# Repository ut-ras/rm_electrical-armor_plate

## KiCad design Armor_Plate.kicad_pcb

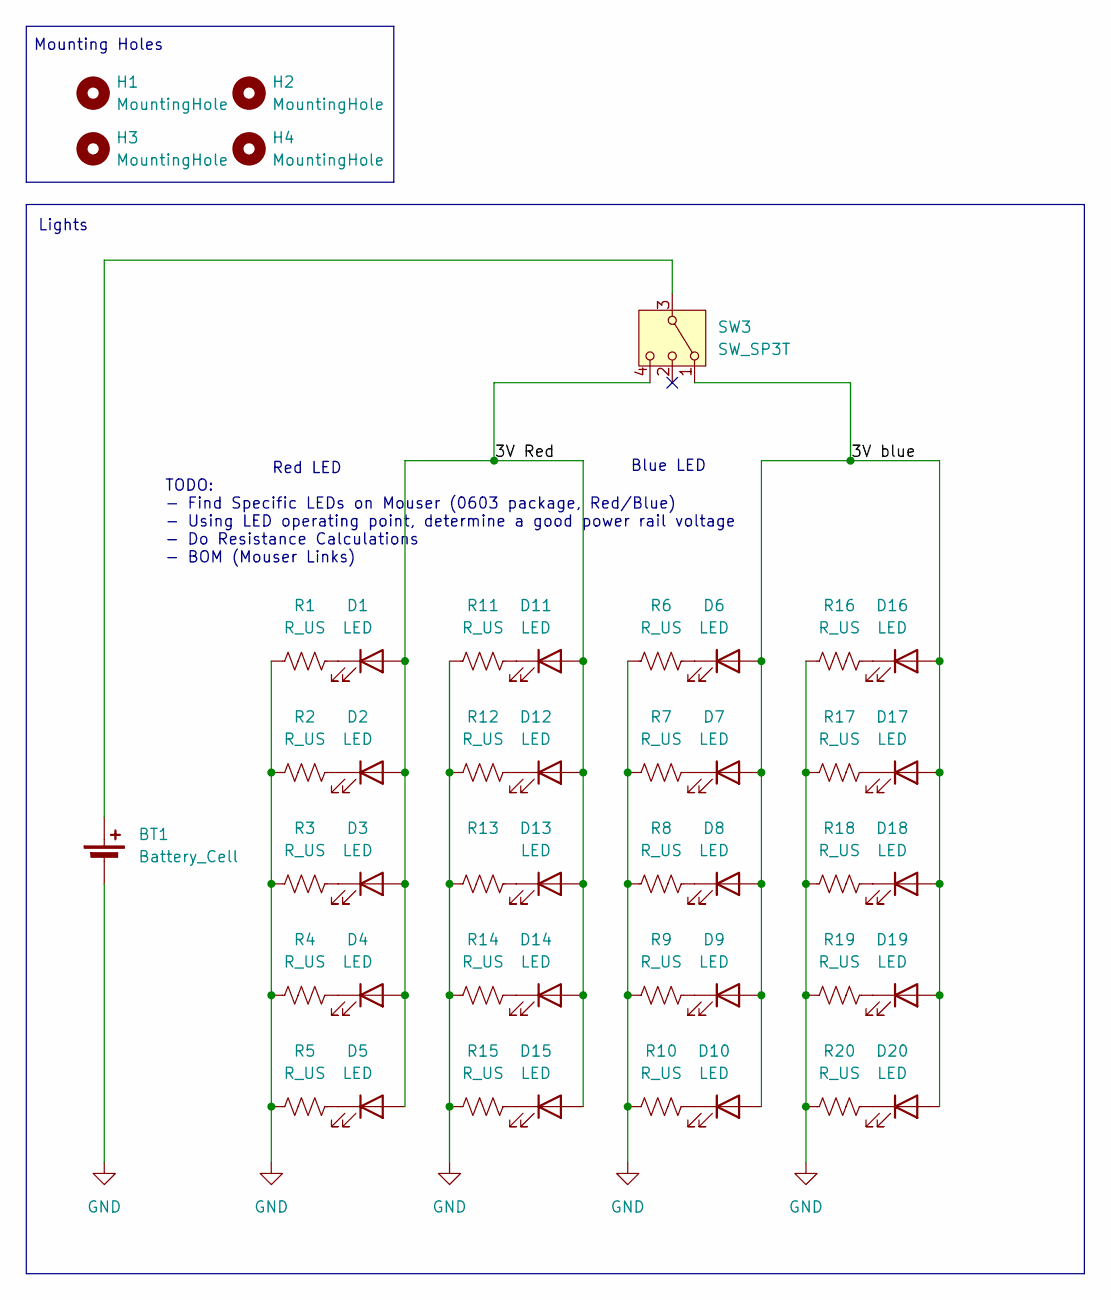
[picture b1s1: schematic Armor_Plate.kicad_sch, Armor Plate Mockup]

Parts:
BT1: Battery_Cell; BatteryHolder_Keystone_2479_3xAAA; Mouser Part Number 613-MN1500-144
D1, D2, D3, D4, D5, D6, D7, D8, D9, D10, D11, D12, D13, D14, D15, D16, D17, D18, D19, D20: LED; LED_0603_1608Metric_Pad1.05x0.95mm_HandSolder; Mouser Part Number 710-150060SS75000
H1, H2, H3, H4: MountingHole; MountingHole_4.5mm
R1, R2, R3, R4, R5, R6, R7, R8, R9, R10, R11, R12, R13, R14, R15, R16, R17, R18, R19, R20: R_US; R_0603_1608Metric_Pad0.98x0.95mm_HandSolder; Mouser Part Number 71-WSLP25125L000FEA
SW3: SW_SP3T; EG1315AA

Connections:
/3V Red: D1.2 (A), D2.2 (A), D3.2 (A), D4.2 (A), D5.2 (A), D11.2 (A), D12.2 (A), D13.2 (A), D14.2 (A), D15.2 (A), SW3.4
/3V blue: D6.2 (A), D7.2 (A), D8.2 (A), D9.2 (A), D10.2 (A), D16.2 (A), D17.2 (A), D18.2 (A), D19.2 (A), D20.2 (A), SW3.1
GND: BT1.2 (-), R1.1, R2.1, R3.1, R4.1, R5.1, R6.1, R7.1, R8.1, R9.1, R10.1, R11.1, R12.1, R13.1, R14.1, R15.1, R16.1, R17.1, R18.1, R19.1, R20.1
unnamed: BT1.1 (+), SW3.3
unnamed: D1.1 (K), R1.2
unnamed: D2.1 (K), R2.2
unnamed: D3.1 (K), R3.2
unnamed: D4.1 (K), R4.2
unnamed: D5.1 (K), R5.2
unnamed: D6.1 (K), R6.2
unnamed: D7.1 (K), R7.2
unnamed: D8.1 (K), R8.2
unnamed: D9.1 (K), R9.2
unnamed: D10.1 (K), R10.2
unnamed: D11.1 (K), R11.2
unnamed: D12.1 (K), R12.2
unnamed: D13.1 (K), R13.2
unnamed: D14.1 (K), R14.2
unnamed: D15.1 (K), R15.2
unnamed: D16.1 (K), R16.2
unnamed: D17.1 (K), R17.2
unnamed: D18.1 (K), R18.2
unnamed: D19.1 (K), R19.2
unnamed: D20.1 (K), R20.2

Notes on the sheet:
Lights
Blue LED
Red LED
TODO: - Find Specific LEDs on Mouser (0603 package, Red/Blue) - Using LED operating point, determine a good power rail voltage - Do Resistance Calculations - BOM (Mouser Links)
Mounting Holes

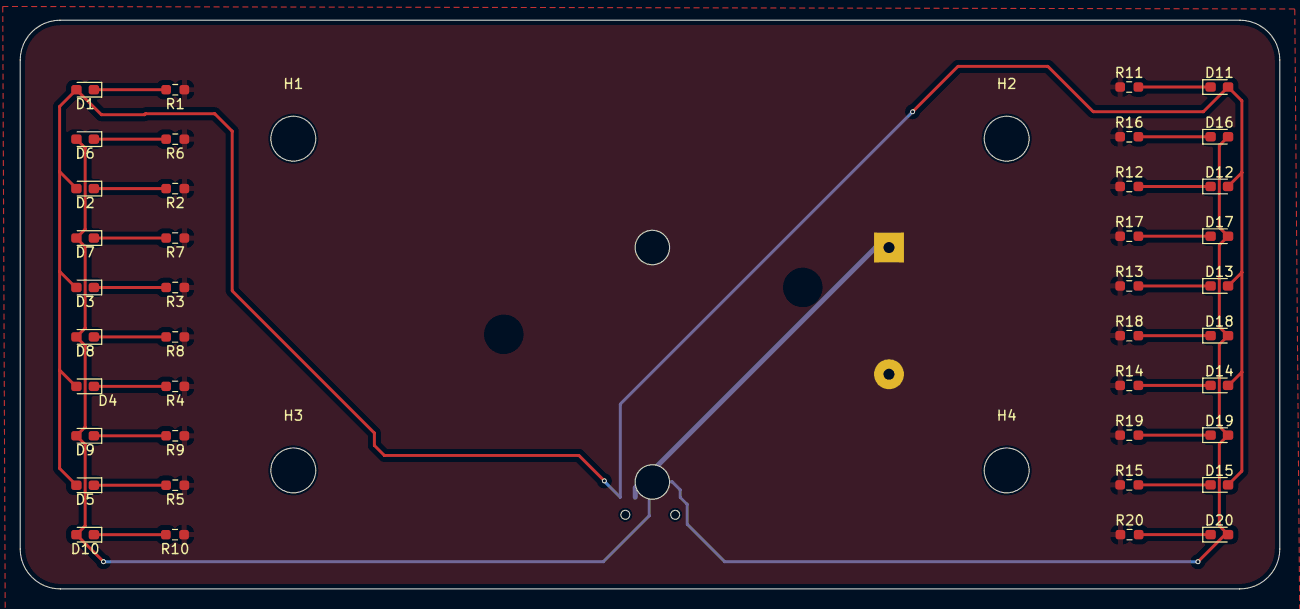
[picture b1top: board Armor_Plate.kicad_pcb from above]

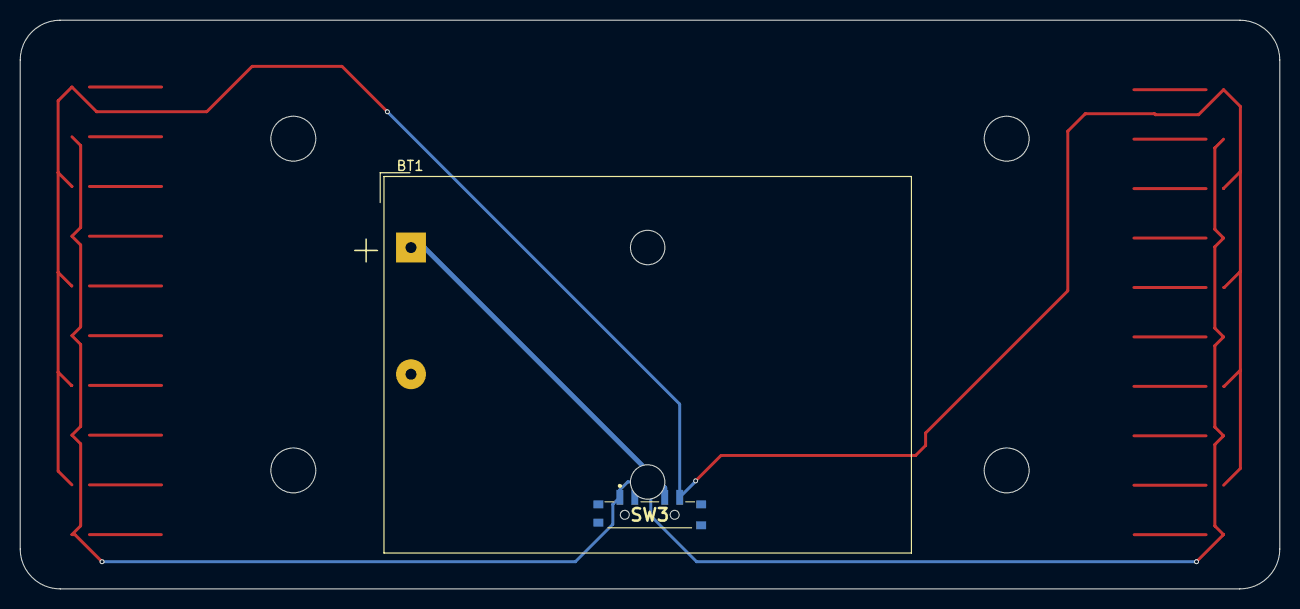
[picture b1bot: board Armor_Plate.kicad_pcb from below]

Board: 2 copper layers, 126.3 x 57.0 mm, 46 parts (2 on the bottom side), 24 nets.

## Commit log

2024-10-14 Updated ArmorPlate project dir name to be consistent
2025-01-27 Renamed project files for consistency
2025-02-08 updated schematic using sp3t switch
2025-02-15 updated pcb footprint for armorplate
2025-02-15 final armorplate pcb with sp3t toggle switch
2025-02-21 fabrication files for armorplate
2025-02-21 gerbfileszip
2025-03-21 Added project-level library submodule
2025-03-21 point library to main branch
2025-03-22 Update library to checkout on submodule update
2025-03-22 Rename project, update fp/sym tables
2025-03-24 Staged work for Armor Plate team
2025-03-25 Updated fab files
2025-03-25 Staged for further work by armor plate team
2025-03-28 Updated Armor Plate 2 batteries
2025-04-04 Changed battery cell footprint to hold 3 batteries
